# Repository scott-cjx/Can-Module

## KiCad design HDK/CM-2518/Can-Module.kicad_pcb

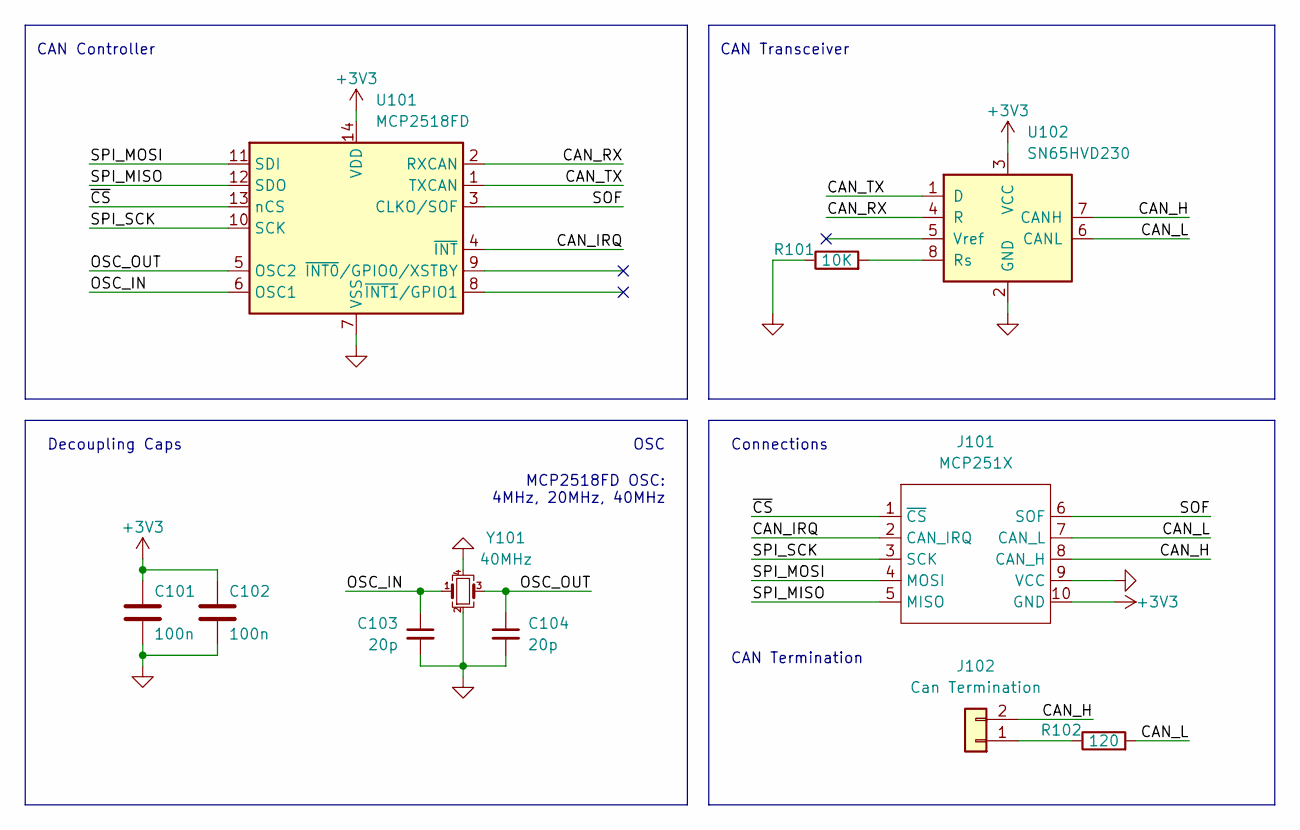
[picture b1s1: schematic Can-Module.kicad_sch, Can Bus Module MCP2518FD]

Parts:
C101, C102: 100n; C_0402_1005Metric; LCSC C1523
C103, C104: 20p; C_0402_1005Metric; LCSC C1554
J101: MCP251X; Can-Module-CM251X
J102: Can Termination; PinHeader_1x02_P2.54mm_Horizontal
R101: 10K; R_0402_1005Metric; LCSC C25744
R102: 120; R_0805_2012Metric; LCSC C17437
U101: MCP2518FD; SOIC-14_3.9x8.7mm_P1.27mm; LCSC C626758
U102: SN65HVD230; SOIC-8_3.9x4.9mm_P1.27mm; LCSC C12084
Y101: 40MHz; Crystal_SMD_3225-4Pin_3.2x2.5mm; LCSC C9010

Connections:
+3V3: C101.1, C102.1, J101.10 (GND), U101.14 (VDD), U102.3 (VCC)
/CAN_H: J101.8 (CAN_H), U102.7 (CANH); also elsewhere on the board
/CAN_IRQ: J101.2 (CAN_IRQ), U101.4 (~INT)
/CAN_L: J101.7 (CAN_L), R102.2, U102.6 (CANL)
/CAN_RX: U101.2 (RXCAN), U102.4 (R)
/CAN_TX: U101.1 (TXCAN), U102.1 (D)
/OSC_IN: C103.1, U101.6 (OSC1), Y101.1
/OSC_OUT: C104.1, U101.5 (OSC2), Y101.3
/SOF: J101.6 (SOF), U101.3 (CLKO/SOF)
/SPI_MISO: J101.5 (MISO), U101.12 (SDO)
/SPI_MOSI: J101.4 (MOSI), U101.11 (SDI)
/SPI_SCK: J101.3 (SCK), U101.10 (SCK)
/~CS: J101.1 (~CS), U101.13 (nCS)
GND: C101.2, C102.2, C103.2, C104.2, J101.9 (VCC), R101.1, U101.7 (VSS), U102.2 (GND), Y101.2, Y101.4
unnamed: J102.1, R102.1
unnamed: R101.2, U102.8 (Rs)

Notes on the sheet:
Decoupling Caps
OSC
CAN Termination
MCP2518FD OSC: 4MHz, 20MHz, 40MHz
CAN Controller
Connections
CAN Transceiver

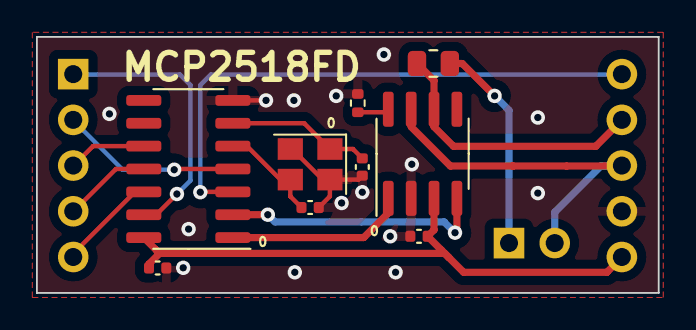
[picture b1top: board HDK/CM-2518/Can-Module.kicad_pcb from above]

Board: 2 copper layers, 34.5 x 14.2 mm, 11 parts (0 on the bottom side), 15 nets.

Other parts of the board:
J103: Can Termination; PinHeader_1x02_P2.54mm_Horizontal

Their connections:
/CAN_H: J103.2; also elsewhere on the board

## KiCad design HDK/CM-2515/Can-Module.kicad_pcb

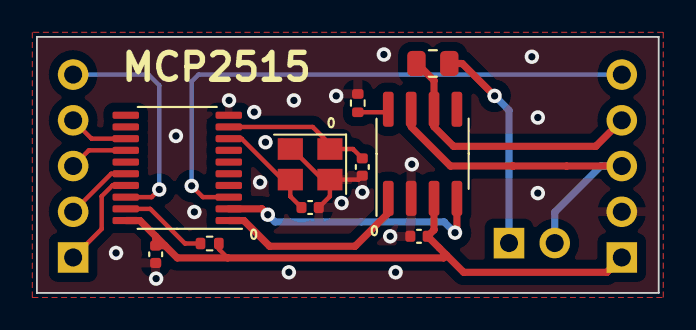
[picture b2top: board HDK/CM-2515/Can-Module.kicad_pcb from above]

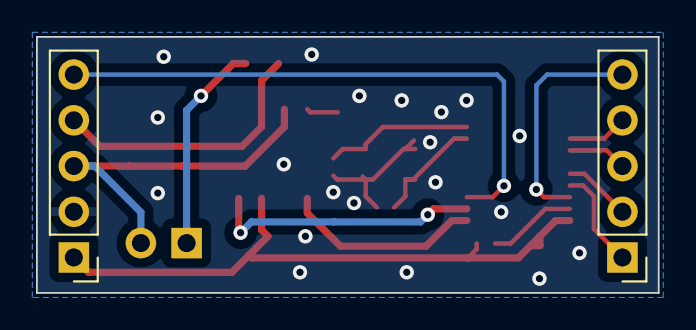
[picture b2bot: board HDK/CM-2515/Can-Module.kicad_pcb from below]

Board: 2 copper layers, 34.5 x 14.2 mm, 13 parts (2 on the bottom side), 17 nets.

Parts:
C101, C102: 100n; C_0402_1005Metric
C103, C104: 20p; C_0402_1005Metric
J101, J102: Can Connect; PinHeader_1x05_P2.54mm_Vertical
J103: Can Termination; PinHeader_1x02_P2.54mm_Horizontal
R101, R102: 10K; R_0402_1005Metric
R103: 120; R_0805_2012Metric
U101: SN65HVD230; SOIC-8_3.9x4.9mm_P1.27mm
U102: MCP2515-xST; TSSOP-20_4.4x6.5mm_P0.65mm
Y101: 40MHz; Crystal_SMD_3225-4Pin_3.2x2.5mm

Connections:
+3V3: C101.1, C102.1, J102.1, R102.2, U101.3 (VCC), U102.20 (VDD)
/CAN_H: J102.3, J103.2, U101.7 (CANH)
/CAN_IRQ: J101.4, U102.13 (~INT)
/CAN_L: J102.4, R103.2, U101.6 (CANL)
/CAN_RX: U101.4 (R), U102.2 (RXCAN)
/CAN_TX: U101.1 (D), U102.1 (TXCAN)
/OSC_IN: C103.1, U102.9 (OSC1), Y101.1
/OSC_OUT: C104.1, U102.8 (OSC2), Y101.3
/SOF: J102.5, U102.3 (CLKOUT/SOF)
/SPI_MISO: J101.1, U102.17 (SO)
/SPI_MOSI: J101.2, U102.16 (SI)
/SPI_SCK: J101.3, U102.14 (SCK)
/~CS: J101.5, U102.18 (~CS)
GND: C101.2, C102.2, C103.2, C104.2, J102.2, R101.1, U101.2 (GND), U102.10 (VSS), Y101.2, Y101.4
unnamed: J103.1, R103.1
unnamed: R101.2, U101.8 (Rs)
unnamed: R102.1, U102.19 (~RESET)

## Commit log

2023-12-08 Initialize gh-pages
2023-12-08 Moving files docs/* LICENSE using main
2023-12-08 Deploying to gh-pages from @ scott-cjx/Can-Module@caee52f2d83aa73e6c6c335e6598c543d3964038 🚀
2023-12-08 added mcp2515 module
2023-12-08 Deploying to gh-pages from @ scott-cjx/Can-Module@bdd10715dc081803b8c0c54f34198e4669dc5408 🚀
2023-12-10 added fd module
2023-12-10 Deploying to gh-pages from @ scott-cjx/Can-Module@4e73bcafb4d28d812847110bf36b77a50336cb73 🚀
2023-12-10 updated CM-2518FD Module
2023-12-10 Deploying to gh-pages from @ scott-cjx/Can-Module@9dab0b65401b73a04653998e2e1a0b41830beb01 🚀
2023-12-10 updated CM2515
2023-12-10 Deploying to gh-pages from @ scott-cjx/Can-Module@5de0b2ffd475ebe864dbff6d101bc95fe065f2cf 🚀
2023-12-20 updated can-module
2023-12-20 Deploying to gh-pages from @ scott-cjx/Can-Module@66a13b2f272bb1a91ce73b2120ca5de2f6669de4 🚀
